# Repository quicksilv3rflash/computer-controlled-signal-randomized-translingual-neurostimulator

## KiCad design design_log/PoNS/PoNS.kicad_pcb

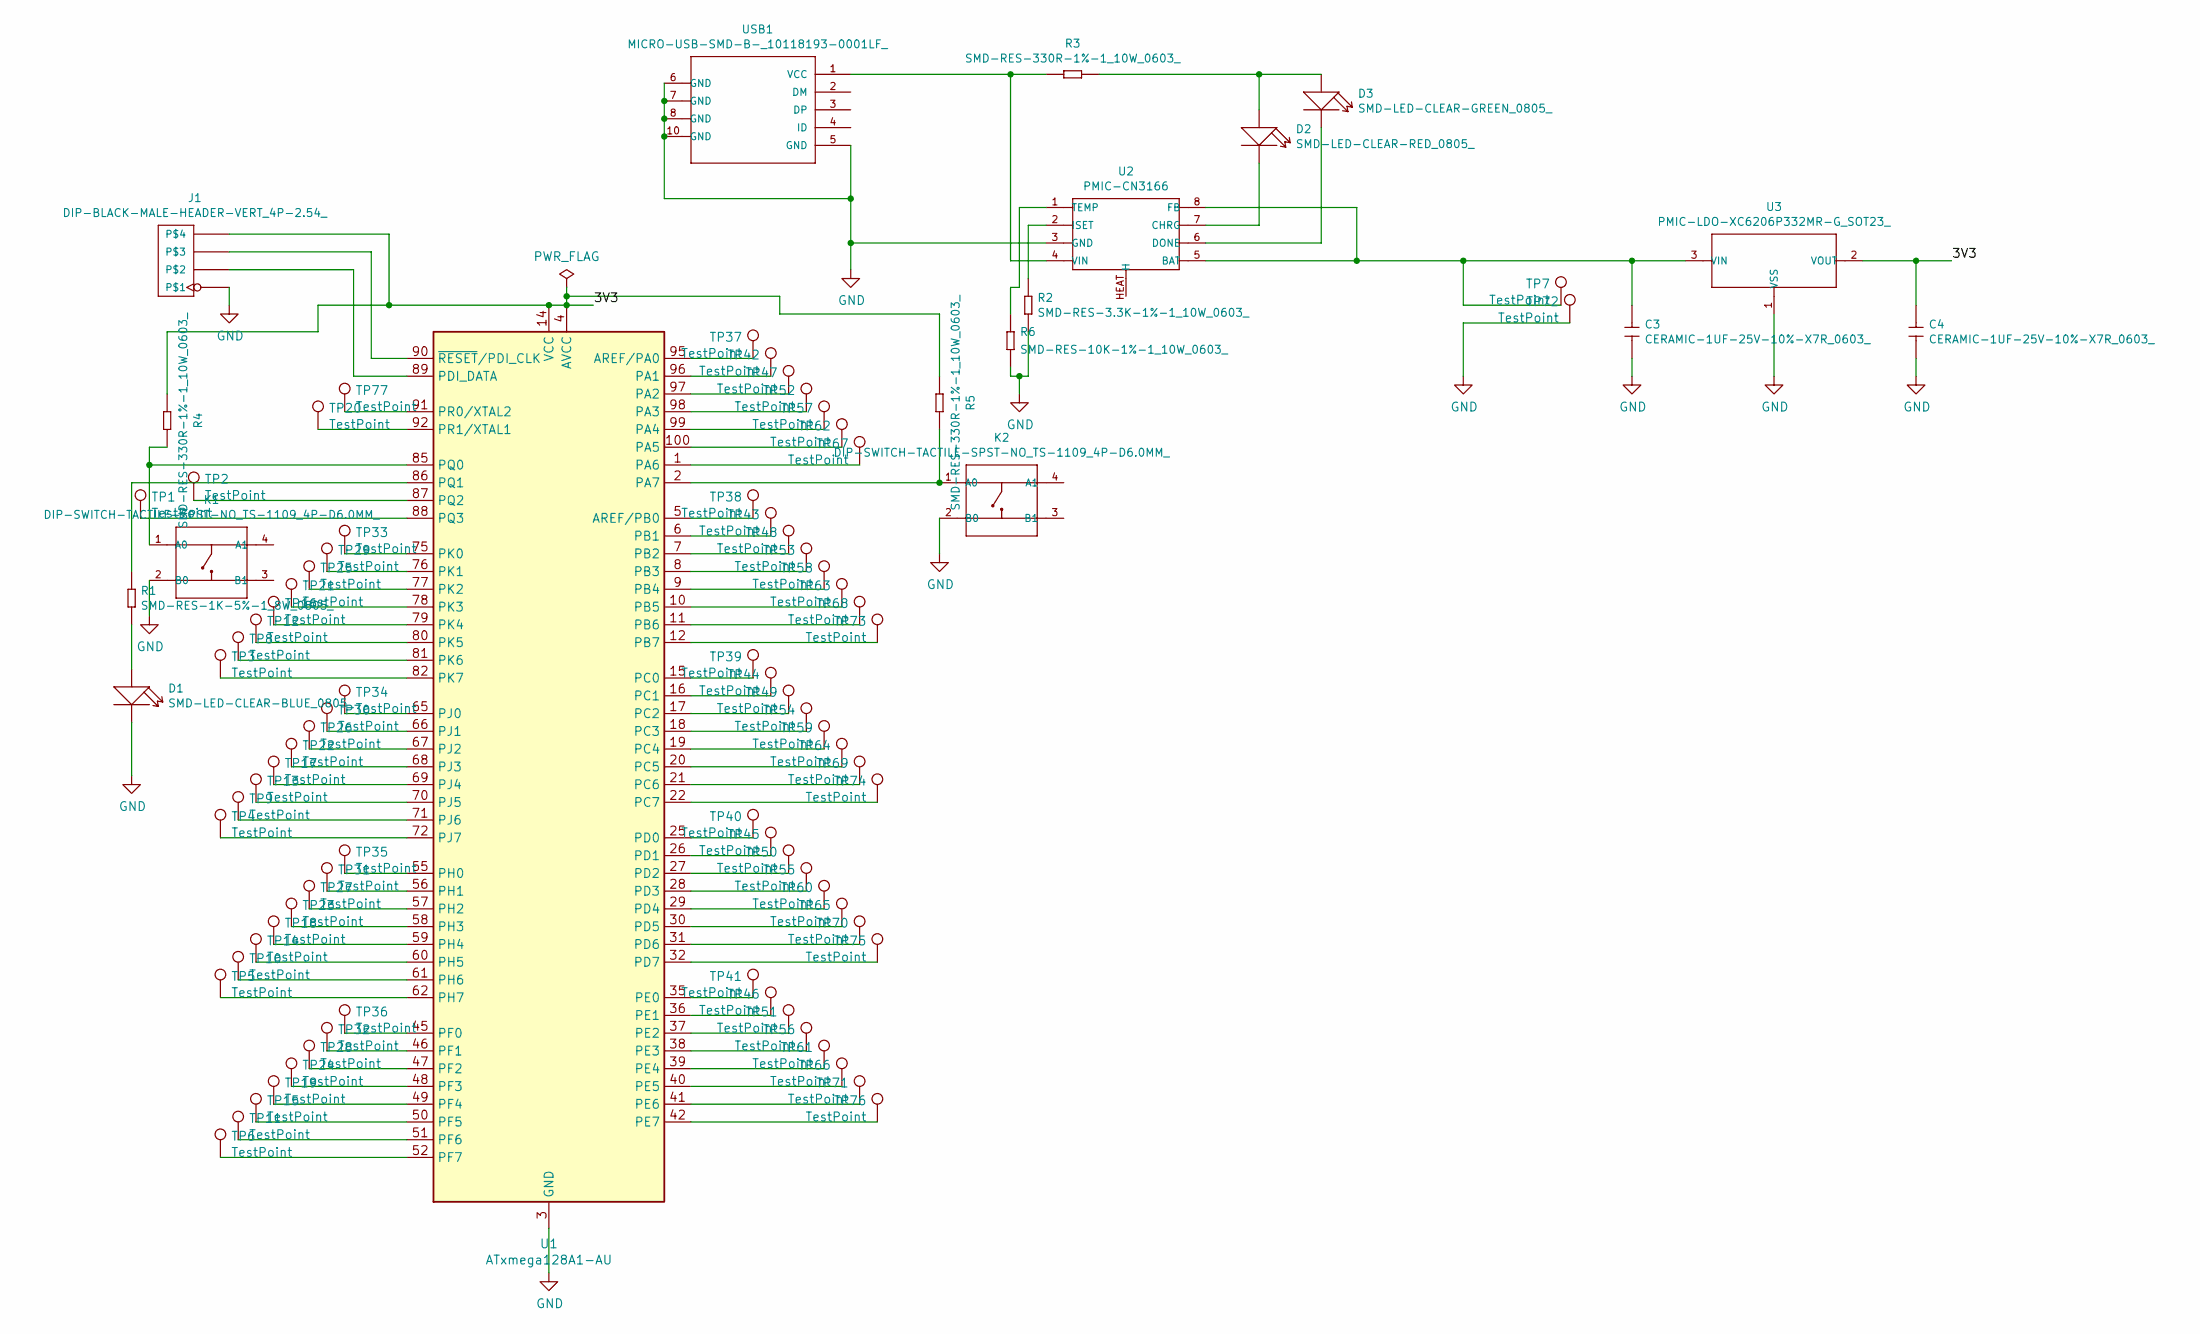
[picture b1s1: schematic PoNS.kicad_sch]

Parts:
C3, C4: CERAMIC-1UF-25V-10%-X7R_0603_; C0603; MPN CC0603KRX7R8BB105
D1: SMD-LED-CLEAR-BLUE_0805_; LED-0805; MPN EL-17-215_BHC-AN1P2_3T
D2: SMD-LED-CLEAR-RED_0805_; LED-0805; MPN 17-215SURC_S530-A2_TR8
D3: SMD-LED-CLEAR-GREEN_0805_; LED-0805; MPN 17-215SYGC_S530-E2_TR8
J1: DIP-BLACK-MALE-HEADER-VERT_4P-2.54_; H4-2.54; MPN P125-1104A0BS116A1
K1, K2: DIP-SWITCH-TACTILE-SPST-NO_TS-1109_4P-D6.0MM_; SW4-6.0X6.0X5.0MM
R1: SMD-RES-1K-5%-1_8W_0805_; R0805; MPN RC0805JR-071KL
R2: SMD-RES-3.3K-1%-1_10W_0603_; R0603; MPN RC0603FR-073K3L
R3, R4, R5: SMD-RES-330R-1%-1_10W_0603_; R0603; MPN RC0603FR-07330RL
R6: SMD-RES-10K-1%-1_10W_0603_; R0603; MPN RC0603FR-0710KL
TP1, TP2, TP3, TP4, TP5, TP6, TP8, TP9, TP10, TP11, TP12, TP13, TP14, TP15, TP16, TP17, TP18, TP19, TP20, TP21, TP22, TP23, TP24, TP25, TP26, TP27, TP28, TP29, TP30, TP31, TP32, TP33, TP34, TP35, TP36, TP37, TP38, TP39, TP40, TP41, TP42, TP43, TP44, TP45, TP46, TP47, TP48, TP49, TP50, TP51, TP52, TP53, TP54, TP55, TP56, TP57, TP58, TP59, TP60, TP61, TP62, TP63, TP64, TP65, TP66, TP67, TP68, TP69, TP70, TP71, TP73, TP74, TP75, TP76, TP77: TestPoint; TestPoint_Pad_1.0x1.0mm
TP7, TP72: TestPoint; SolderWire-0.75sqmm_1x01_D1.25mm_OD2.3mm
U1: ATxmega128A1-AU; TQFP-100_14x14mm_P0.5mm
U2: PMIC-CN3166; DFN8G-0.5-3X3MM; MPN CN3065
U3: PMIC-LDO-XC6206P332MR-G_SOT23_; SOT-23; MPN XC6206P332MR-G
USB1: MICRO-USB-SMD-B-_10118193-0001LF_; MICRO-USB5+6P-SMD-0.65-B; MPN 10118193-0001LF

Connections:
/3V3: C4.1, J1.4, R4.1, R5.1, U1.4 (AVCC), U1.14 (VCC), U1.24 (VCC), U1.34 (VCC), U1.44 (VCC), U1.54 (VCC), U1.64 (VCC), U1.74 (VCC), U1.83 (VCC), U1.94 (AVCC), U3.2 (VOUT)
GND: C3.2, C4.2, D1.2 (-), J1.1, K1.2 (B0), K2.2 (B0), R2.2, R6.2, TP72.1, U1.3 (GND), U1.13 (GND), U1.23 (GND), U1.33 (GND), U1.43 (GND), U1.53 (GND), U1.63 (GND), U1.73 (GND), U1.84 (GND), U1.93 (GND), U2.3 (GND), U3.1 (VSS), USB1.5 (GND), USB1.6 (GND), USB1.7 (GND), USB1.8 (GND), USB1.9 (GND), USB1.10 (GND), USB1.11 (GND)
unnamed: D1.1 (+), R1.2
unnamed: D2.1 (+), D3.1 (+), R3.2
unnamed: D2.2 (-), U2.7 (CHRG)
unnamed: D3.2 (-), U2.6 (DONE)
unnamed: J1.2, U1.89 (PDI_DATA)
unnamed: J1.3, U1.90 (~RESET/PDI_CLK)
unnamed: K1.1 (A0), R4.2, U1.85 (PQ0)
unnamed: K2.1 (A0), R5.2, U1.2 (PA7)
unnamed: TP37.1, U1.95 (AREF/PA0)
unnamed: TP38.1, U1.5 (AREF/PB0)
unnamed: TP42.1, U1.96 (PA1)
unnamed: TP47.1, U1.97 (PA2)
unnamed: TP52.1, U1.98 (PA3)
unnamed: TP57.1, U1.99 (PA4)
unnamed: TP62.1, U1.100 (PA5)
unnamed: TP67.1, U1.1 (PA6)
unnamed: TP43.1, U1.6 (PB1)
unnamed: TP48.1, U1.7 (PB2)
unnamed: TP53.1, U1.8 (PB3)
unnamed: TP58.1, U1.9 (PB4)
unnamed: TP63.1, U1.10 (PB5)
unnamed: TP68.1, U1.11 (PB6)
unnamed: TP73.1, U1.12 (PB7)
unnamed: TP39.1, U1.15 (PC0)
unnamed: TP44.1, U1.16 (PC1)
unnamed: TP49.1, U1.17 (PC2)
unnamed: TP54.1, U1.18 (PC3)
unnamed: TP59.1, U1.19 (PC4)
unnamed: TP64.1, U1.20 (PC5)
unnamed: TP69.1, U1.21 (PC6)
unnamed: TP74.1, U1.22 (PC7)
unnamed: TP40.1, U1.25 (PD0)
unnamed: TP45.1, U1.26 (PD1)
unnamed: TP50.1, U1.27 (PD2)
unnamed: TP55.1, U1.28 (PD3)
unnamed: TP60.1, U1.29 (PD4)
unnamed: TP65.1, U1.30 (PD5)
unnamed: TP70.1, U1.31 (PD6)
unnamed: TP75.1, U1.32 (PD7)
unnamed: TP41.1, U1.35 (PE0)
unnamed: TP46.1, U1.36 (PE1)
unnamed: TP51.1, U1.37 (PE2)
unnamed: TP56.1, U1.38 (PE3)
unnamed: TP61.1, U1.39 (PE4)
unnamed: TP66.1, U1.40 (PE5)
unnamed: TP71.1, U1.41 (PE6)
unnamed: TP76.1, U1.42 (PE7)
unnamed: TP36.1, U1.45 (PF0)
unnamed: TP32.1, U1.46 (PF1)
unnamed: TP28.1, U1.47 (PF2)
unnamed: TP24.1, U1.48 (PF3)
unnamed: TP19.1, U1.49 (PF4)
unnamed: TP15.1, U1.50 (PF5)
unnamed: TP11.1, U1.51 (PF6)
unnamed: TP6.1, U1.52 (PF7)
unnamed: TP35.1, U1.55 (PH0)
unnamed: TP31.1, U1.56 (PH1)
unnamed: TP27.1, U1.57 (PH2)
unnamed: TP23.1, U1.58 (PH3)
unnamed: TP18.1, U1.59 (PH4)
unnamed: TP14.1, U1.60 (PH5)
unnamed: TP10.1, U1.61 (PH6)
unnamed: TP5.1, U1.62 (PH7)
unnamed: TP34.1, U1.65 (PJ0)
unnamed: TP30.1, U1.66 (PJ1)
unnamed: TP26.1, U1.67 (PJ2)
unnamed: TP22.1, U1.68 (PJ3)
unnamed: TP17.1, U1.69 (PJ4)
unnamed: TP13.1, U1.70 (PJ5)
unnamed: TP9.1, U1.71 (PJ6)
unnamed: TP4.1, U1.72 (PJ7)
unnamed: TP33.1, U1.75 (PK0)
unnamed: TP29.1, U1.76 (PK1)
unnamed: TP25.1, U1.77 (PK2)
unnamed: TP21.1, U1.78 (PK3)
unnamed: TP16.1, U1.79 (PK4)
unnamed: TP12.1, U1.80 (PK5)
unnamed: TP8.1, U1.81 (PK6)
unnamed: TP3.1, U1.82 (PK7)
unnamed: R1.1, U1.86 (PQ1)
unnamed: TP2.1, U1.87 (PQ2)
unnamed: TP1.1, U1.88 (PQ3)
unnamed: TP77.1, U1.91 (PR0/XTAL2)
unnamed: TP20.1, U1.92 (PR1/XTAL1)
unnamed: C3.1, TP7.1, U2.5 (BAT), U2.8 (FB), U3.3 (VIN)
unnamed: R2.1, U2.2 (ISET)
unnamed: R6.1, U2.1 (TEMP)
unnamed: R3.1, U2.4 (VIN), USB1.1 (VCC)

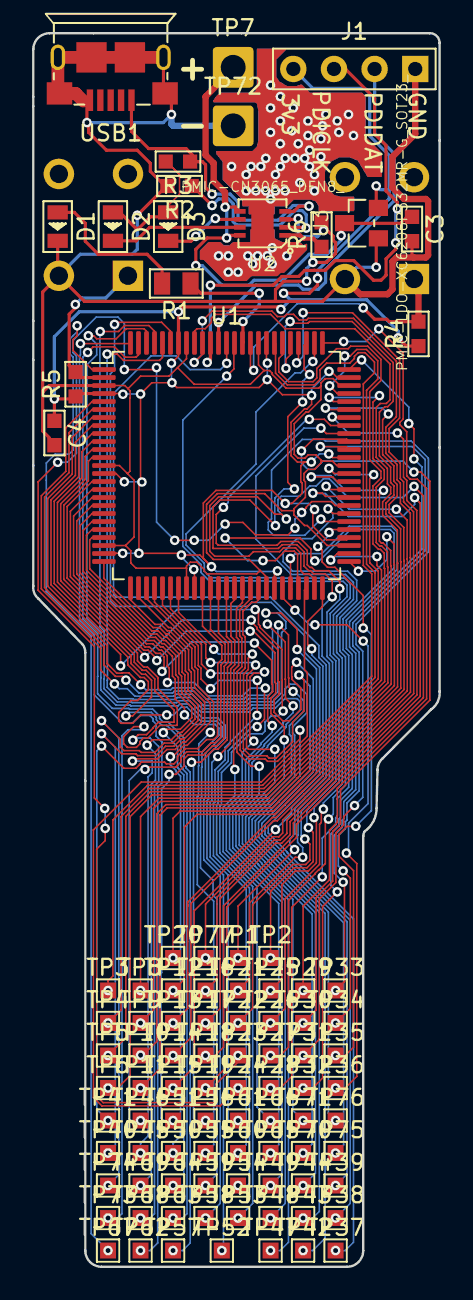
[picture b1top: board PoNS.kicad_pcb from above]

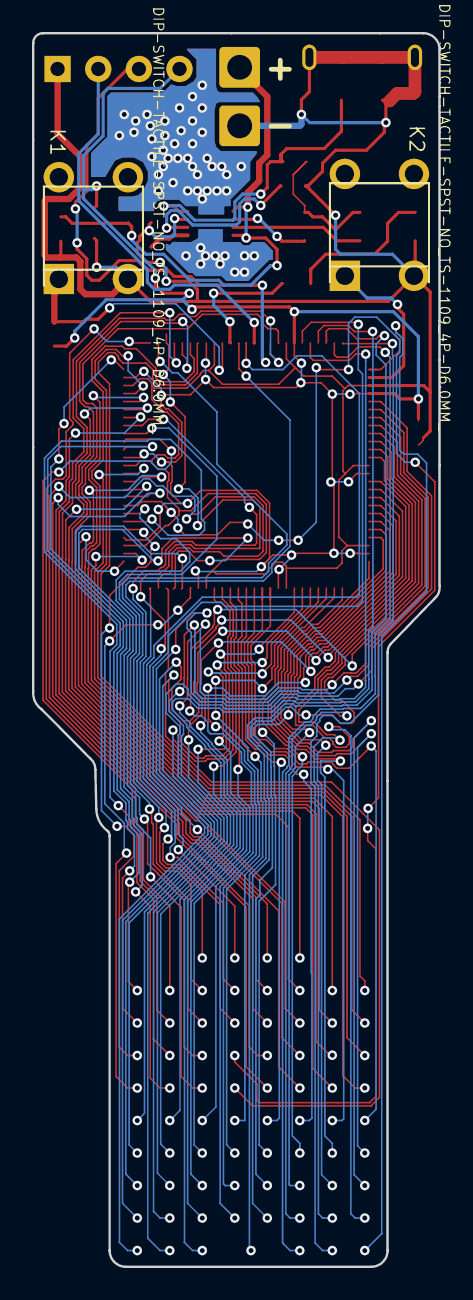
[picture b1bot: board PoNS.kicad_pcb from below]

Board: 2 copper layers, 25.4 x 77.1 mm, 95 parts (2 on the bottom side), 90 nets.

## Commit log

2026-05-09 Continue filling in design log
2026-05-09 Finish filling in design log
2026-05-09 Added published documentation
2026-05-11 Added Serial.setTimeout(50); to reduce latency
2026-05-11 Updated build instructions
